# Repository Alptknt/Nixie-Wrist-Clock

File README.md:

# Nixie Wrist Clock
 2 Digit Nixie wrist clock

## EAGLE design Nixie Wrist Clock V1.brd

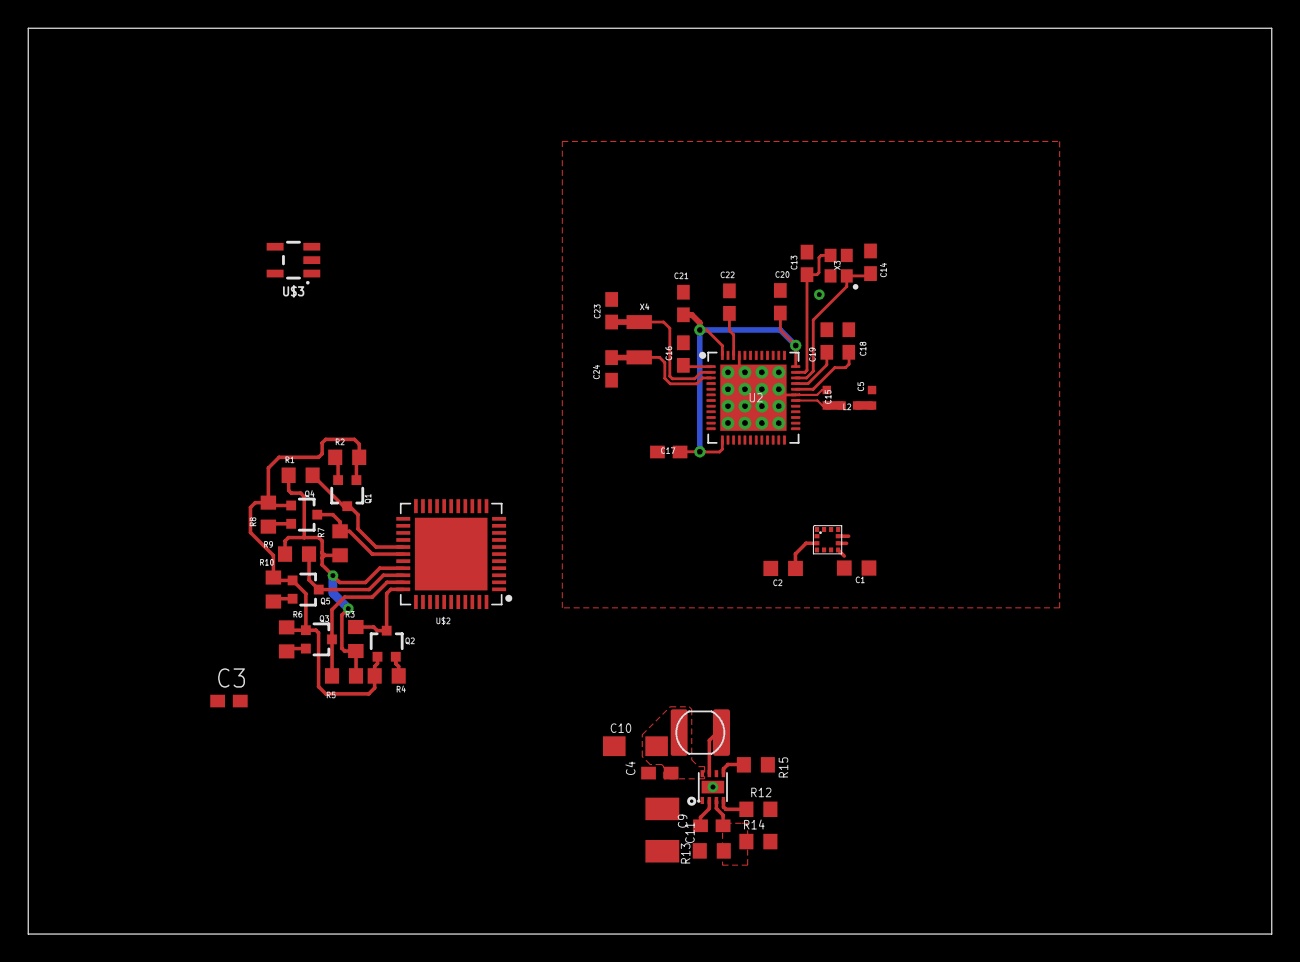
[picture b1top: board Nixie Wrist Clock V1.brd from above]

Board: 2 copper layers, 88.1 x 64.2 mm, 48 parts (0 on the bottom side), 28 nets.

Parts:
C1, C2: 100nF; C0603K
C3, C4, C16, C17, C20: 100nF; RESC0603_N
C5, C15: 1pF; RESC0402_N
C9, C19: 100pF; RESC0603_N
C10: 10uF; SMC_A
C11: 22uF; SMC_B
C13, C14, C23, C24: 12pF; RESC0603_N
C18: N.M.; RESC0603_N
C21: 4.7µF; RESC0603_N
C22: 1.0µF; RESC0603_N
L2: 3.9nH; RESC0402_N
Q1, Q2, Q3, Q4, Q5: 310mA/60V/1.6Ω; SOT323
R1, R2, R3, R4, R5, R6, R7, R8, R9, R10: 10K; R0603
R12: 6.65K; R0603
R13: 768K; R0603
R14: 243K; R0603
R15: 868K; R0603
U2: NRF52832; QFN40P600X600X90-48_N
U$1: BMA400; LGA-12
U$2: HV5523K7; QFN50P707X707X80-45T515
U$3: TLV70233SOT23-5; SOT23-5
U$4: TPS61252DSGR; WSON-8-PAD
U$5: FPI-SERIES-INDUCTOR0302; FPI-0302
X3: 32MHz; BT-XTAL_2016_N
X4: 32.768kHz; XTAL_3215_N

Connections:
+3V3: C1.2, C2.1, C3.1, C17.1, C20.1, C21.1, Q1.1, Q2.1, Q3.1, Q4.1, Q5.1, R2.2, R4.2, R6.2, R8.2, R10.2, U2.13, U2.36, U2.48, U$1.3, U$1.7, U$3.5
+5V: C9.1, C11.+, R1.2, R3.2, R5.2, R7.2, R9.2, R13.1, R15.1, U$2.30, U$4.2
ANT1: C15.1, L2.1, U2.30
BL: Q2.3, R3.1, U$2.33
CLK: Q4.3, R7.1, U$2.28
DATAIN: Q3.3, R5.1, U$2.32
DEC1: C16.1, U2.1
DEC2: C18.1, U2.32
DEC3: C19.1, U2.33
DEC4: C22.1, U2.46
GND: C1.1, C2.2, C3.2, C4.2, C5.2, C10.-, C11.-, C13.2, C14.2, C15.2, C16.2, C17.2, C18.2, C19.2, C20.2, C21.2, C22.2, C23.1, C24.1, R12.2, R14.2, U2.31, U2.45, U2.PAD, U2.PAD@VIA01, U2.PAD@VIA02, U2.PAD@VIA03, U2.PAD@VIA04, U2.PAD@VIA05, U2.PAD@VIA06, U2.PAD@VIA07, U2.PAD@VIA08, U2.PAD@VIA09, U2.PAD@VIA10, U2.PAD@VIA11, U2.PAD@VIA12, U2.PAD@VIA13, U2.PAD@VIA14, U2.PAD@VIA15, U2.PAD@VIA16, U$1.8, U$1.9, U$2.29, U$2.45, U$3.2, U$3.4, U$4.1, U$4.PAD, X3.2, X3.4
LE: Q5.3, R9.1, U$2.31
unnamed: C13.1, U2.35, X3.3
unnamed: Q1.2, R2.1
unnamed: Q2.2, R4.1
unnamed: U$4.7, U$5.P$2
unnamed: Q3.2, R6.1
unnamed: R12.1, U$4.4
unnamed: Q4.2, R8.1
unnamed: R15.2, U$4.5
unnamed: Q5.2, R10.1
unnamed: C9.2, R13.2, R14.1, U$4.3
P0.00/XL1: C23.2, U2.2, X4.1
P0.01/XL2: C24.2, U2.3, X4.2
POL: Q1.3, R1.1, U$2.27
RF: C5.1, L2.2
VCC: C4.1, C10.+, U$3.1, U$4.8, U$5.P$1
X2: C14.1, U2.34, X3.1

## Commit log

2019-09-06 Update (Alp)
2019-09-14 alp update
2019-09-17 3v3 LDO added
2019-10-02 Update #6
    5V Supply IC added
2019-10-02 Revert "Update #6"
    This reverts commit 39989620e637334a808b500ab2563335b83f3b38.
2019-10-13 Update#7
    5V Boost Regulator Added
2019-10-13 Update#7
2019-10-13 asd
    asd
2019-10-13 Update #8
2019-10-13 Revert "Update #8"
    This reverts commit 503de56c1cec5e58df481c359deaf8b3a9d703f1.

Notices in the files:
parts and their libraries:
SparkFun-DiscreteSemi: Licensing: Creative Commons ShareAlike 4.0 International - https://creativecommons.org/licenses/by-sa/4.0
